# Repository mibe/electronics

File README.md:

# This repo contains some electronic projects of mine:

## Arduino
Some simple codes for the Arduino platform

## Blaulicht
Retrofitting an old toy car with emergency lights

## BreadBoard-Power-BusBar
Connect both opposing supply rails of a breadboard in an orderly fashion

## breakout_boards
Some breakout boards for use on a breadboard

## cookie-mouse
An automatic clicking mouse for the game Cookie Clicker

## Feuermelder
A USB "keyboard" disguised in the form of a fire call point to open the Windows Taskmanager

## Flip-USB
A replacement USB board for JBL's Flip 2 bluetooth speaker

## LCR-Shoe
A power supply attachment for cheap LCR meters

## StarPower
A control PCB for a christmas star as a replacement for the old, less energy-efficient one

## thunder-timer
A device to calculate thunderstorm distance by timing the interval between lightning and thunder

## tiny-UPDI-burner
A small board for connecting an USB to RS-232 converter to SOIC to DIL converters for burning ATtiny's via UPDI

## uCurrentCase
A case for Dave Jones' µCurrent GOLD

## USB-breaker
A tool to shortly disconnect a USB device from the USB bus

## Wire-to-RJ14
A simple adapter to connect bare wires to a cable with RJ-14 connectors

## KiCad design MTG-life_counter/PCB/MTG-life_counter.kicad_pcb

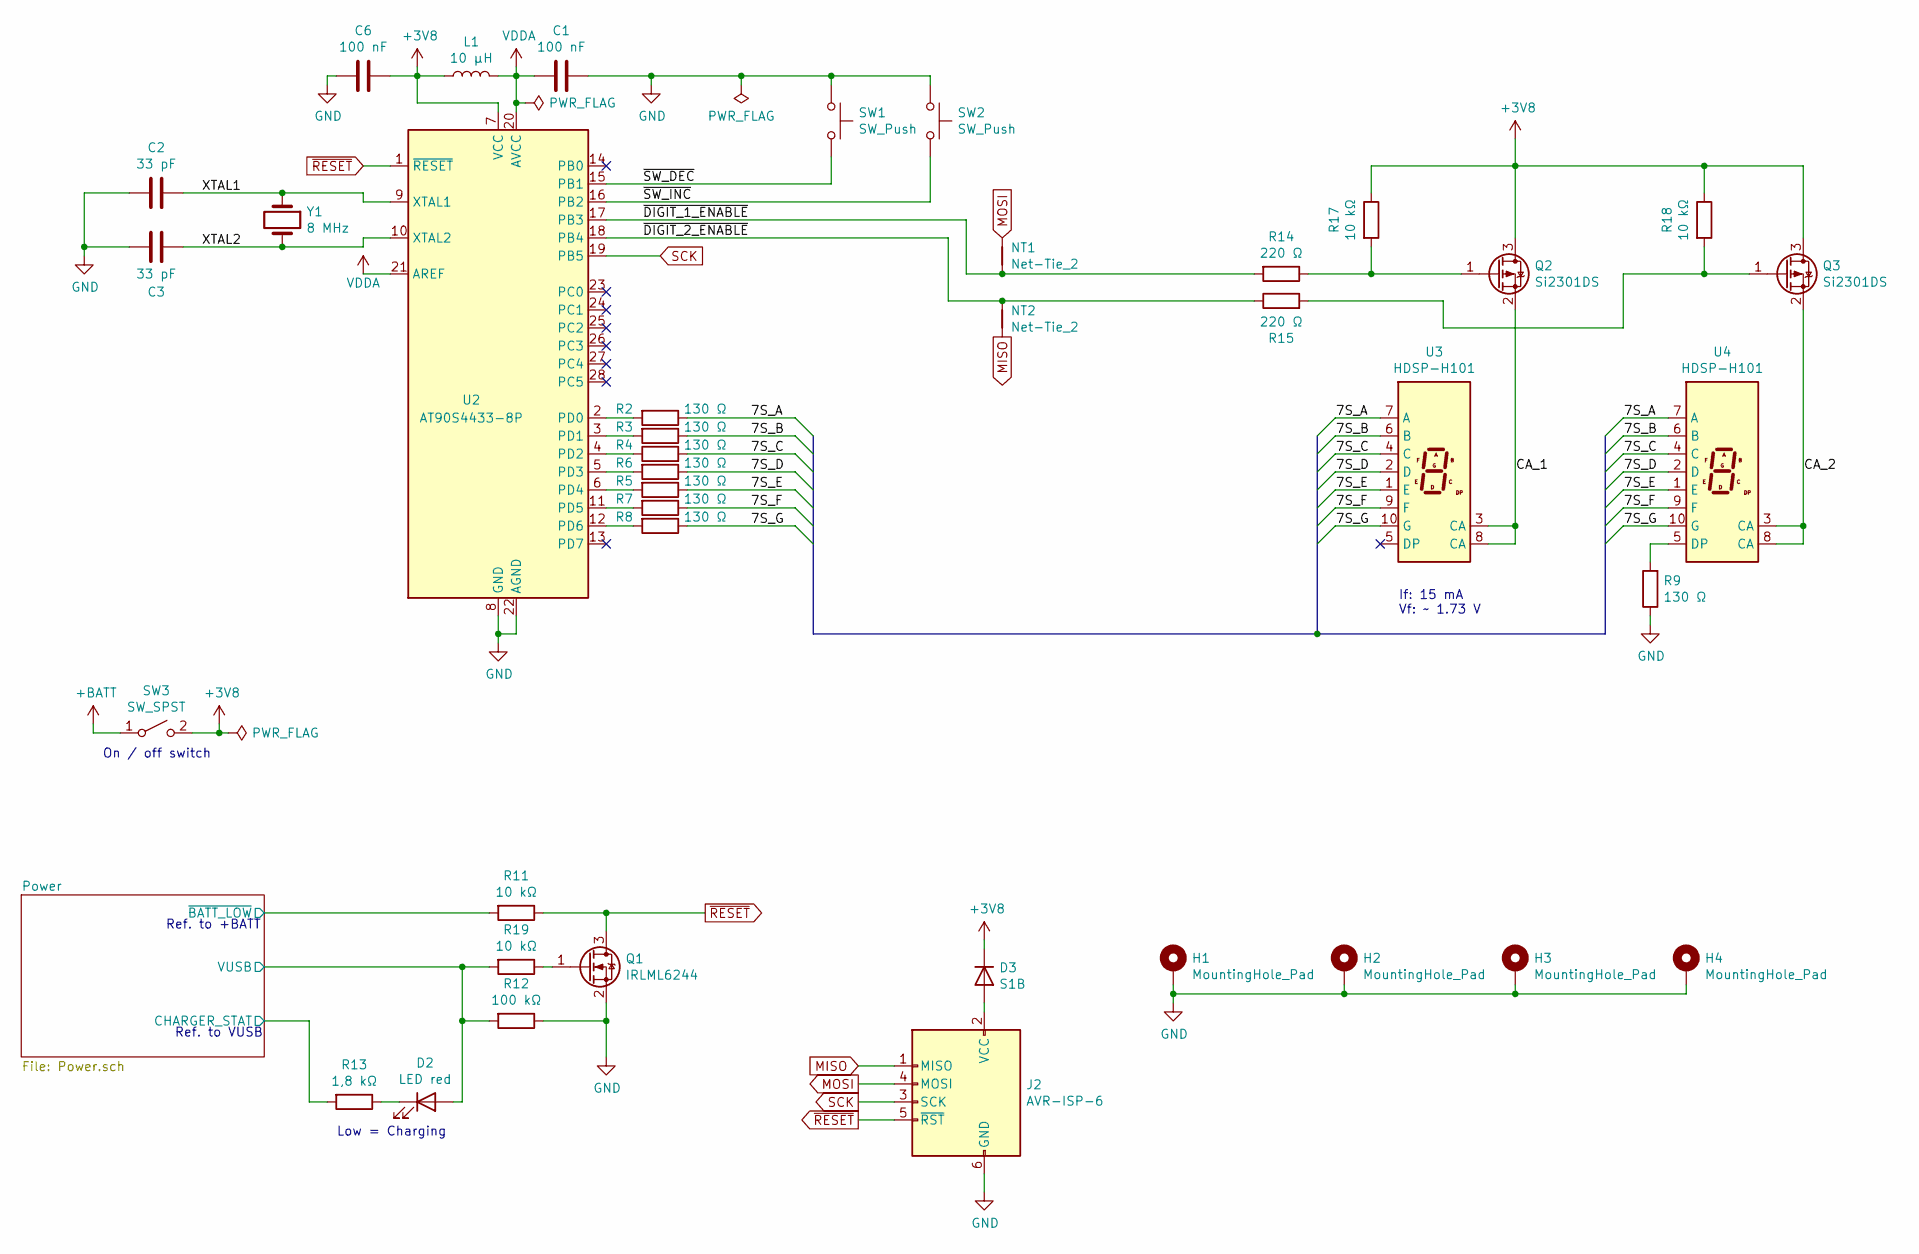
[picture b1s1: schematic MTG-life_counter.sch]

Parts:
C1, C6: 100 nF; C_0805_2012Metric_Pad1.18x1.45mm_HandSolder
C2, C3: 33 pF; C_1206_3216Metric_Pad1.42x1.75mm_HandSolder
D2: LED red; LED_D3.0mm_Horizontal_O1.27mm_Z2.0mm
D3: S1B; D_SMA_Handsoldering
H1, H2, H3, H4: MountingHole_Pad; SMTSO-M3
J2: AVR-ISP-6; PinHeader_2x03_P2.54mm_Vertical
L1: 10 µH; L_0805_2012Metric_Pad1.15x1.40mm_HandSolder
NT1, NT2: Net-Tie_2; NetTie-2_SMD_Pad0.25mm
Q1: IRLML6244; SOT-23_Handsoldering
Q2, Q3: Si2301DS; SOT-23_Handsoldering
R2, R3, R4, R5, R6, R7, R8, R9: 130 Ω; R_0805_2012Metric_Pad1.20x1.40mm_HandSolder
R11, R17, R18, R19: 10 kΩ; R_0805_2012Metric_Pad1.20x1.40mm_HandSolder
R12: 100 kΩ; R_0805_2012Metric_Pad1.20x1.40mm_HandSolder
R13: 1,8 kΩ; R_0805_2012Metric_Pad1.20x1.40mm_HandSolder
R14, R15: 220 Ω; R_0805_2012Metric_Pad1.20x1.40mm_HandSolder
SW1, SW2: SW_Push; SolderWire-0.15sqmm_1x02_P4mm_D0.5mm_OD1.5mm
SW3: SW_SPST; SolderWire-0.15sqmm_1x02_P4mm_D0.5mm_OD1.5mm
U2: AT90S4433-8P; DIP-28_W7.62mm
U3, U4: HDSP-H101
Y1: 8 MHz; Crystal_HC49-4H_Vertical

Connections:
+3V8: C6.1, D3.1 (K), L1.1, Q2.3 (D), Q3.3 (D), R17.1, R18.1, SW3.2 (B), U2.7 (VCC)
+BATT: SW3.1 (A); also elsewhere on the board
/7S_A: R2.1, U3.7 (A), U4.7 (A)
/7S_B: R3.1, U3.6 (B), U4.6 (B)
/7S_C: R4.2, U3.4 (C), U4.4 (C)
/7S_D: R5.1, U3.2 (D), U4.2 (D)
/7S_E: R6.1, U3.1 (E), U4.1 (E)
/7S_F: R7.1, U3.9 (F), U4.9 (F)
/7S_G: R8.1, U3.10 (G), U4.10 (G)
/CA_1: Q2.2 (S), U3.3 (CA), U3.8 (CA)
/CA_2: Q3.2 (S), U4.3 (CA), U4.8 (CA)
/Power/CHARGER_STAT: R13.2; also elsewhere on the board
/Power/VUSB: D2.2 (A), R12.2, R19.2; also elsewhere on the board
/Power/~BATT_LOW: R11.2; also elsewhere on the board
/XTAL1: C2.1, U2.9 (XTAL1), Y1.1
/XTAL2: C3.1, U2.10 (XTAL2), Y1.2
/~DIGIT_1_ENABLE: NT1.2, R14.2, U2.17 (PB3)
/~DIGIT_2_ENABLE: NT2.1, R15.1, U2.18 (PB4)
/~SW_DEC: SW1.2, U2.15 (PB1)
/~SW_INC: SW2.2, U2.16 (PB2)
GND: C1.1, C2.2, C3.2, C6.2, H1.1, H2.1, H3.1, H4.1, J2.6 (GND), Q1.2 (S), R9.1, R12.1, SW1.1, SW2.1, U2.8 (GND), U2.22 (AGND); also elsewhere on the board
MISO: J2.1 (MISO), NT2.2
MOSI: J2.4 (MOSI), NT1.1
unnamed: D2.1 (K), R13.1
unnamed: D3.2 (A), J2.2 (VCC)
unnamed: Q1.1 (G), R19.1
unnamed: Q2.1 (G), R14.1, R17.2
unnamed: Q3.1 (G), R15.2, R18.2
unnamed: R2.2, U2.2 (PD0)
unnamed: R3.2, U2.3 (PD1)
unnamed: R4.1, U2.4 (PD2)
unnamed: R5.2, U2.5 (PD3)
unnamed: R6.2, U2.6 (PD4)
unnamed: R7.2, U2.11 (PD5)
unnamed: R8.2, U2.12 (PD6)
unnamed: R9.2, U4.5 (DP)
SCK: J2.3 (SCK), U2.19 (PB5)
VDDA: C1.2, L1.2, U2.20 (AVCC), U2.21 (AREF)
~RESET: J2.5 (~RST), Q1.3 (D), R11.1, U2.1 (~RESET)

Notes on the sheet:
If: 15 mA Vf: ~~ 1.73 V
Ref. to +BATT
Ref. to VUSB
Low = Charging
On / off switch

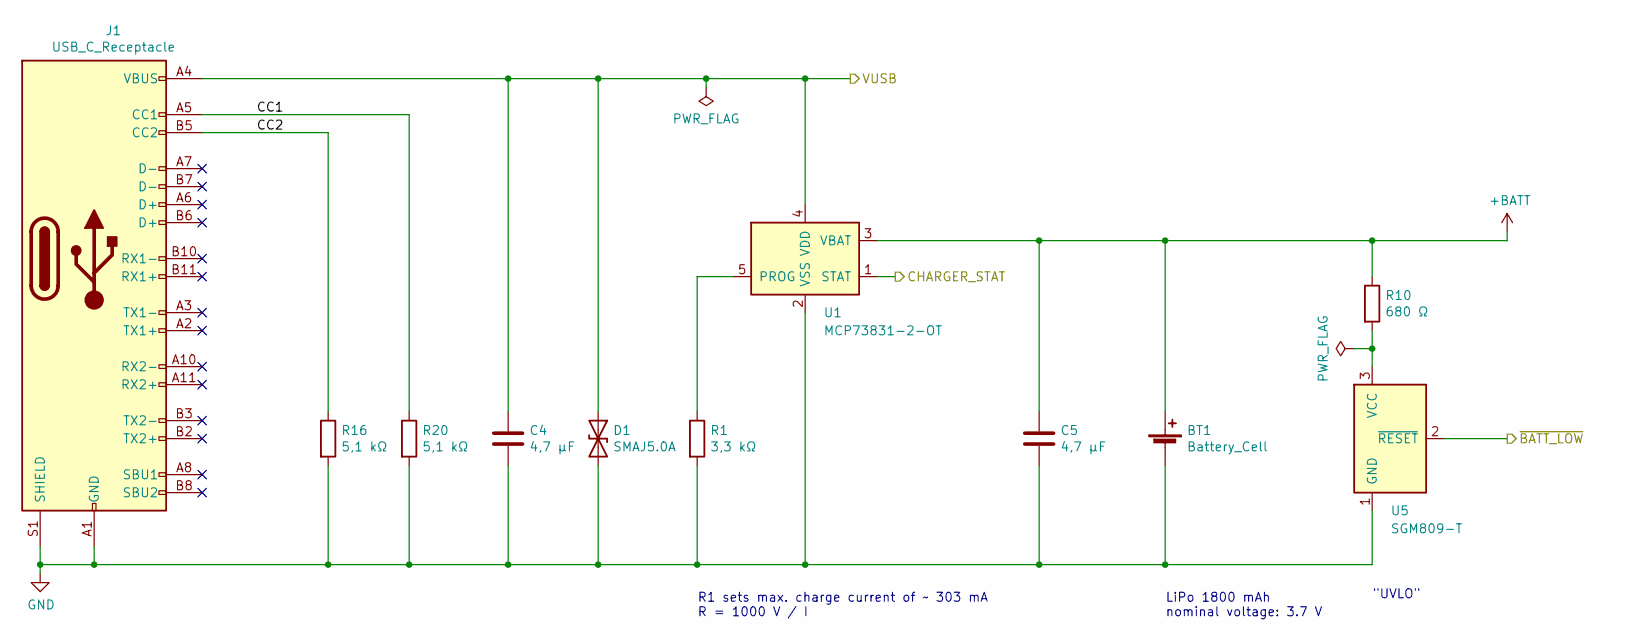
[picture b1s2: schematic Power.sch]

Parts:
BT1: Battery_Cell; PinHeader_1x02_P2.54mm_Horizontal
C4, C5: 4,7 µF; C_1206_3216Metric_Pad1.42x1.75mm_HandSolder
D1: SMAJ5.0A; D_SMA_Handsoldering
J1: USB_C_Receptacle; USB_C_Receptacle_Bellwether_80211-x92
R1: 3,3 kΩ; R_0805_2012Metric_Pad1.20x1.40mm_HandSolder
R10: 680 Ω; R_0805_2012Metric_Pad1.20x1.40mm_HandSolder
R16, R20: 5,1 kΩ; R_0805_2012Metric_Pad1.20x1.40mm_HandSolder
U1: MCP73831-2-OT; SOT-23-5
U5: SGM809-T; SOT-23W_Handsoldering

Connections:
+BATT: BT1.1 (+), C5.1, R10.1, U1.3 (VBAT); also elsewhere on the board
/Power/CC1: J1.A5 (CC1), R20.1
/Power/CC2: J1.B5 (CC2), R16.1
/Power/CHARGER_STAT: U1.1 (STAT); also elsewhere on the board
/Power/VUSB: C4.1, D1.1 (A1), J1.A4 (VBUS), J1.A9 (VBUS), J1.B4 (VBUS), J1.B9 (VBUS), U1.4 (VDD); also elsewhere on the board
/Power/~BATT_LOW: U5.2 (~RESET); also elsewhere on the board
GND: BT1.2 (-), C4.2, C5.2, D1.2 (A2), J1.A1 (GND), J1.A12 (GND), J1.B1 (GND), J1.B12 (GND), J1.S1 (SHIELD), R1.2, R16.2, R20.2, U1.2 (VSS), U5.1 (GND); also elsewhere on the board
unnamed: R1.1, U1.5 (PROG)
unnamed: R10.2, U5.3 (VCC)

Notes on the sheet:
LiPo 1800 mAh nominal voltage: 3.7 V
R1 sets max. charge current of ~~ 303 mA R = 1000 V / I
"UVLO"

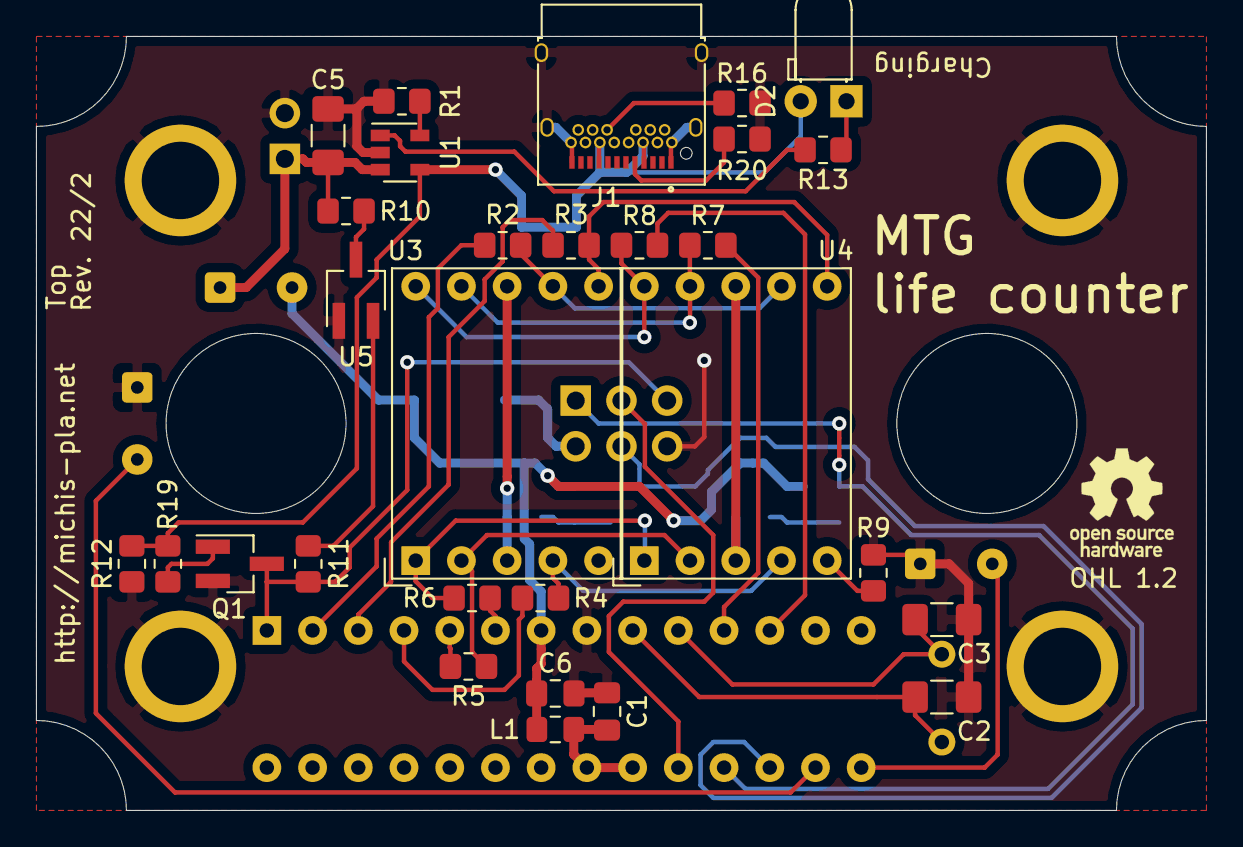
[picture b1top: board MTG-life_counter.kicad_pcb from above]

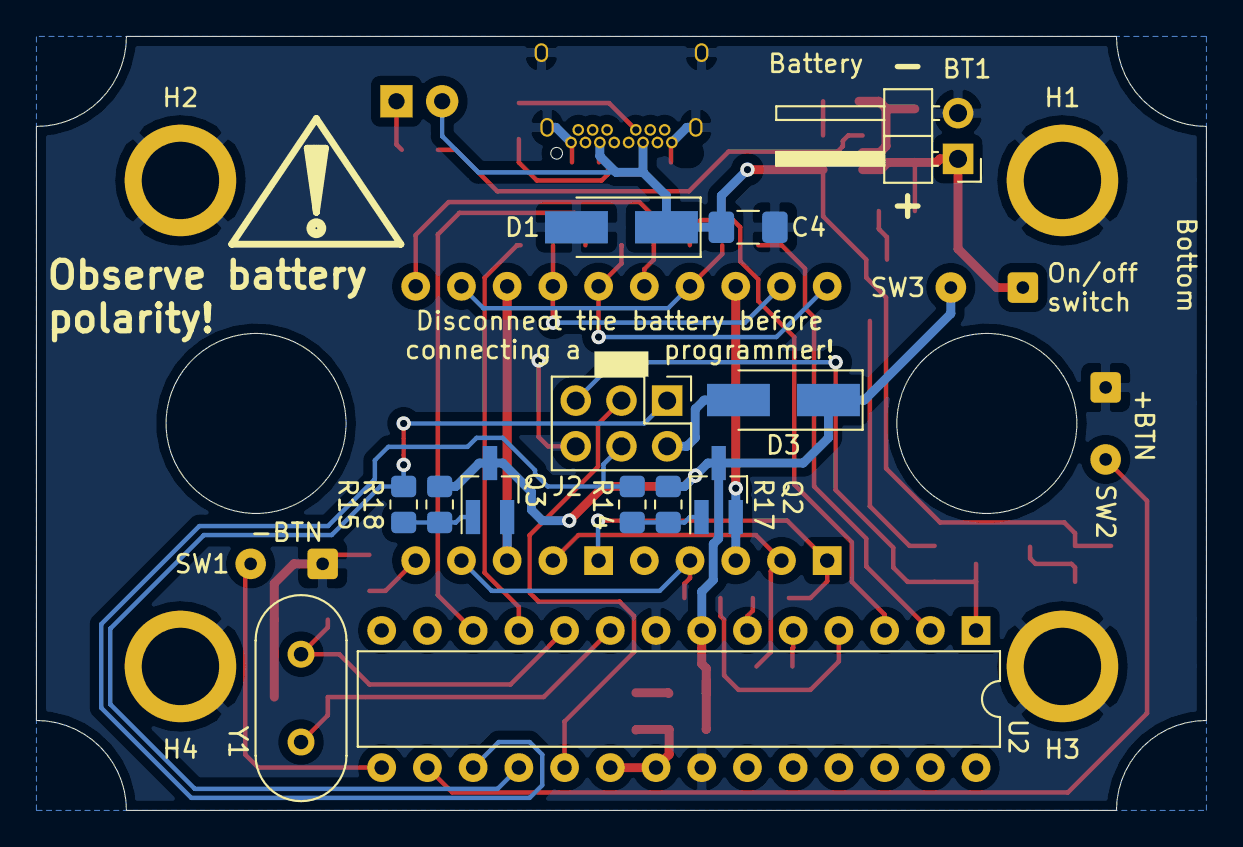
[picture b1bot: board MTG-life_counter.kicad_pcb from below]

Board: 2 copper layers, 65.0 x 43.0 mm, 51 parts (18 on the bottom side), 43 nets.

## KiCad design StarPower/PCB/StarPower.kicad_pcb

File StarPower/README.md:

# StarPower
"StarPower" is a PCB to drive one of these cheap Moravian star christmas decorations. The original circuit drives 12 LEDs in parallel and uses a dropper resistor. That means about ⅓ of the supply voltage is wasted as heat, which is way too much for a battery powered system. The new circuit uses an LED driver (PAM2804 from Diodes Inc.), which is a step-down DC/DC converter with only 0.1 V feedback voltage. As an added bonus this new circuit supports NiMH rechargeable batteries: A battery monitor resets the system at about 3 V, so the three cells cut-off at about 1 V each. The microcontroller is clocked by a 32.768 kHz crystal and has as many features as possible disabled and runs in sleep mode to save power. The µC consumes about 12 µA.

## Parameters
* Voltage range: 3 V - 4.5 V
* LED current: 120 mA
* LED forward voltage: 2.8 V
* LEDs driven in parallel: 12

## Bill of Materials
See the ```PCB\bom.html``` file.

## License
(C) 2022 Michael Bemmerl

This PCB is available under the [CERN OHL 1.2 License](https://www.ohwr.org/project/cernohl/wikis/Documents/CERN-OHL-version-1.2) license.

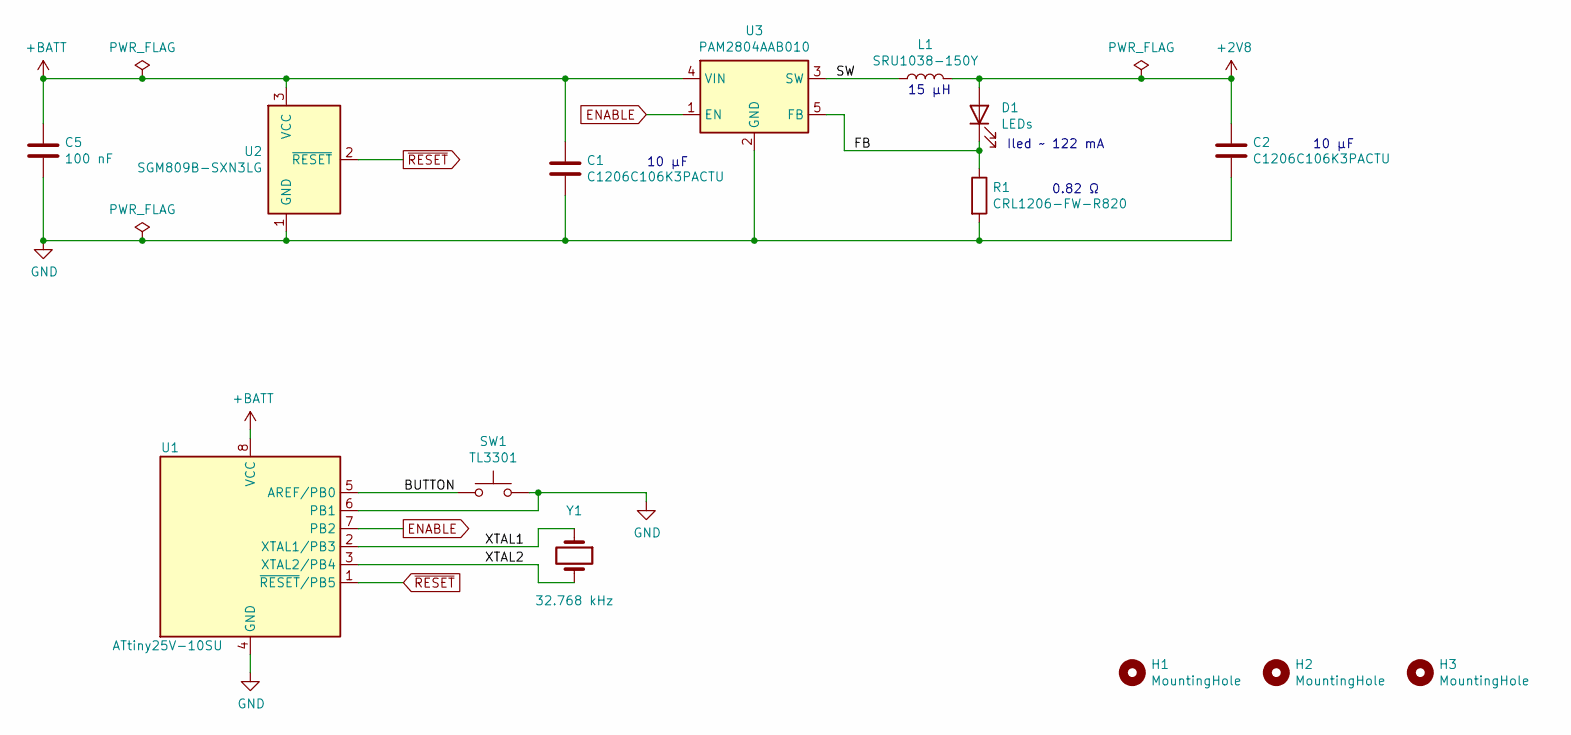
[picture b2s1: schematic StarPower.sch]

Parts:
C1, C2: C1206C106K3PACTU; C_1206_3216Metric_Pad1.42x1.75mm_HandSolder
C5: 100 nF; C_0805_2012Metric_Pad1.18x1.45mm_HandSolder
D1: LEDs
H1, H2: MountingHole; MountingHole_3.5mm
H3: MountingHole; MountingHole_2.5mm
L1: SRU1038-150Y; L_Bourns-SRU1028_10.0x10.0mm
R1: CRL1206-FW-R820; R_1206_3216Metric_Pad1.30x1.75mm_HandSolder
SW1: TL3301; SW_SPST_TL3301
U1: ATtiny25V-10SU; SOIJ-8_5.3x5.3mm_P1.27mm
U2: SGM809B-SXN3LG; SOT-23W_Handsoldering
U3: PAM2804AAB010; TSOT-23-5
Y1: 32.768 kHz; Crystal_SMD_Qantek_QTP7-4Pin_6.9x1.4mm_HandSoldering

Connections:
+2V8: C2.1, D1.2 (A), L1.2
+BATT: C1.1, C5.1, U1.8 (VCC), U2.3 (VCC), U3.4 (VIN)
/BUTTON: SW1.1, U1.5 (AREF/PB0)
/FB: D1.1 (K), R1.1, U3.5 (FB)
/SW: L1.1, U3.3 (SW)
/XTAL1: U1.2 (XTAL1/PB3), Y1.1
/XTAL2: U1.3 (XTAL2/PB4), Y1.2
ENABLE: U1.7 (PB2), U3.1 (EN)
GND: C1.2, C2.2, C5.2, R1.2, SW1.2, U1.4 (GND), U1.6 (PB1), U2.1 (GND), U3.2 (GND)
~RESET: U1.1 (~RESET~/PB5), U2.2 (~RESET)

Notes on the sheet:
15 µH
10 µF
0.82 Ω
Iled ~~ 122 mA

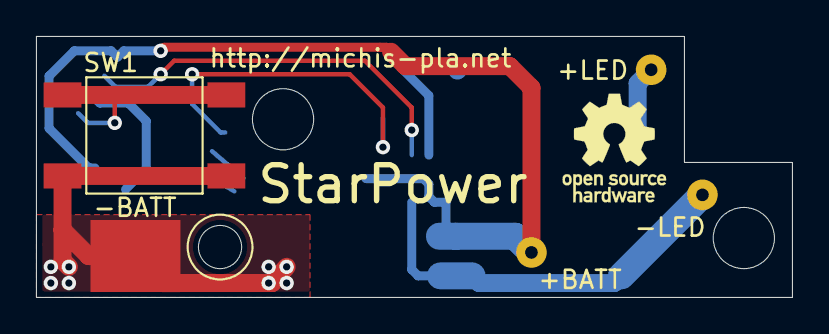
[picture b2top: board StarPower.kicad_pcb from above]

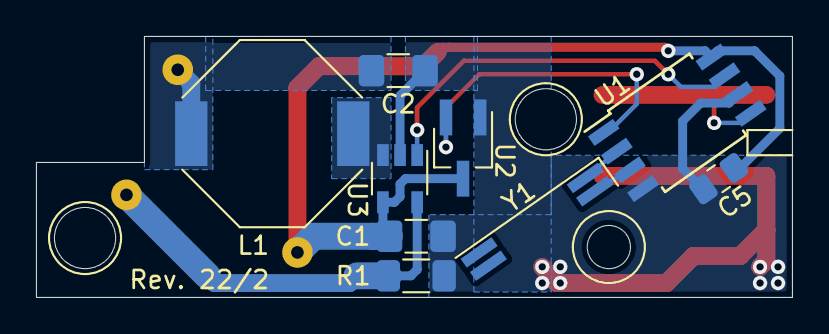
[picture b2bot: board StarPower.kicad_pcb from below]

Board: 2 copper layers, 42.0 x 14.5 mm, 13 parts (9 on the bottom side), 10 nets.

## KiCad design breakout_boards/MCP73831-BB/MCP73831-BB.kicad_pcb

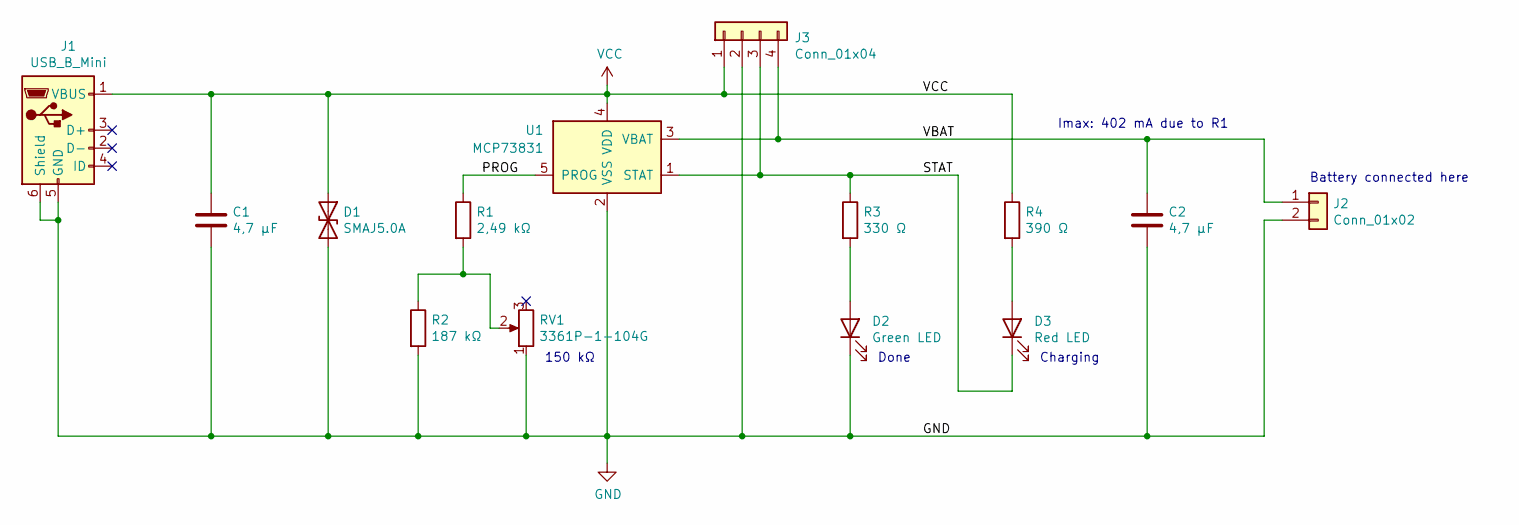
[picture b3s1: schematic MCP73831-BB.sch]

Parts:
C1, C2: 4,7 µF; C_1206_3216Metric_Pad1.42x1.75mm_HandSolder
D1: SMAJ5.0A; D_SMA_Handsoldering
D2: Green LED; LED_1206_3216Metric_Pad1.42x1.75mm_HandSolder
D3: Red LED; LED_1206_3216Metric_Pad1.42x1.75mm_HandSolder
J1: USB_B_Mini; USB_Mini-B_Reichelt_BWM
J2: Conn_01x02; JST_PH_B2B-PH-K_1x02_P2.00mm_Vertical
J3: Conn_01x04; PinHeader_1x04_P2.54mm_Vertical
R1: 2,49 kΩ; R_0805_2012Metric_Pad1.20x1.40mm_HandSolder
R2: 187 kΩ; R_0805_2012Metric_Pad1.20x1.40mm_HandSolder
R3: 330 Ω; R_0805_2012Metric_Pad1.20x1.40mm_HandSolder
R4: 390 Ω; R_0805_2012Metric_Pad1.20x1.40mm_HandSolder
RV1: 3361P-1-104G; Potentiometer_Bourns_3361P_Vertical
U1: MCP73831; SOT-23-5

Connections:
/PROG: R1.1, U1.5 (PROG)
/STAT: D3.1 (K), J3.3, R3.1, U1.1 (STAT)
/VBAT: C2.1, J2.1, J3.4, U1.3 (VBAT)
GND: C1.2, C2.2, D1.2 (A2), D2.1 (K), J1.5 (GND), J1.6 (Shield), J2.2, J3.2, R2.2, RV1.1, U1.2 (VSS)
unnamed: D2.2 (A), R3.2
unnamed: D3.2 (A), R4.2
unnamed: R1.2, R2.1, RV1.2
VCC: C1.1, D1.1 (A1), J1.1 (VBUS), J3.1, R4.1, U1.4 (VDD)

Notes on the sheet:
Imax: 402 mA due to R1
Battery connected here
150 kΩ
Charging
Done

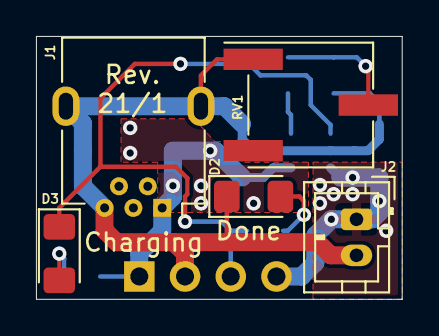
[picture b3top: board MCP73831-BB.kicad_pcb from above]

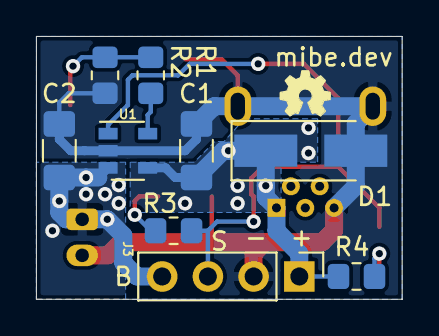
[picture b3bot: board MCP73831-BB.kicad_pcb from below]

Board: 2 copper layers, 20.3 x 14.6 mm, 14 parts (9 on the bottom side), 8 nets.

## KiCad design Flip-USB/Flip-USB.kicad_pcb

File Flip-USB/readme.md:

A replacement USB connector board for JBL's Flip 2 bluetooth speaker, using a Hirose ZX62D-B-5PA8(30) Micro B connector.

The board must have a thickness of 1 mm, otherwise it won't fit into the case of the speaker.

On the original board were two footprints, probably resistors, which were not placed.

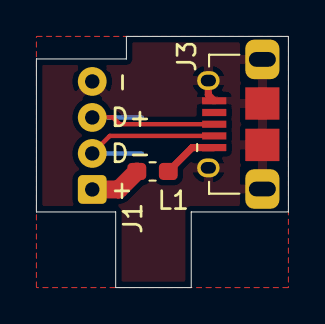
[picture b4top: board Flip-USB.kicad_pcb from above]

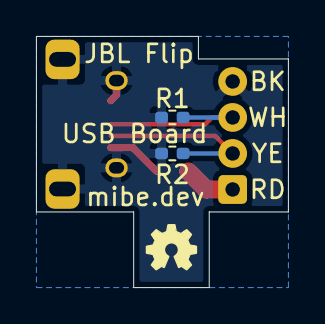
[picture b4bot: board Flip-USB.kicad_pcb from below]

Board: 2 copper layers, 14.0 x 14.0 mm, 5 parts (2 on the bottom side), 5 nets.

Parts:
J1: Conn_01x04; SolderWire-0.15sqmm_1x04_P2mm_D0.5mm_OD1.5mm
J3: ZX62D-B-5PA8(30); USB_Micro_B_Hirose_ZX62D-B-5PA8
L1: ?; L_0603_1608Metric_Pad1.05x0.95mm_HandSolder
R1, R2: R; R_0402_1005Metric_Pad0.72x0.64mm_HandSolder

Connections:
/D+: J1.3, J3.3, R1.1
/D-: J1.2, J3.2, R2.1
/VCC_USB: J3.1, L1.2
GND: J1.4, J3.5, J3.6, R1.2, R2.2
VCC: J1.1, L1.1

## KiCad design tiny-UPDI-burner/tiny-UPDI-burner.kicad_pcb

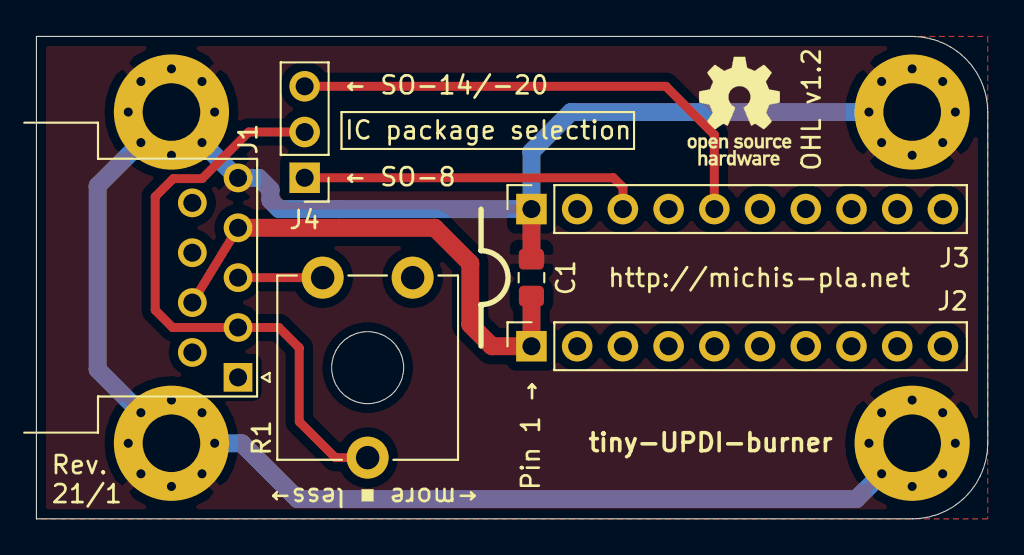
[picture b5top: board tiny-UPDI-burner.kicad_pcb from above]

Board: 2 copper layers, 52.9 x 26.8 mm, 10 parts (0 on the bottom side), 6 nets.

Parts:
C1: 100n; C_0805_2012Metric_Pad1.15x1.40mm_HandSolder
H1, H2, H3, H4: MountingHole_Pad; MountingHole_3.2mm_M3_Pad_Via
J1: DB9_Female; DSUB-9_Female_Horizontal_P2.77x2.54mm_EdgePinOffset9.40mm
J2, J3: Conn_01x10_Female; PinSocket_1x10_P2.54mm_Vertical
J4: Conn_01x03_Male; PinHeader_1x03_P2.54mm_Vertical
R1: 10k; Potentiometer_ACP_CA9-V10_Vertical_Hole

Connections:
/RxD: J1.2, J4.2, R1.2
/TxD: J1.3, R1.1
/UPDI_8: J3.3, J4.1
/UPDI_14-20: J3.5, J4.3
GND: C1.2, H1.1, H2.1, H3.1, H4.1, J1.5, J3.1
VCC: C1.1, J1.4, J1.7, J2.1

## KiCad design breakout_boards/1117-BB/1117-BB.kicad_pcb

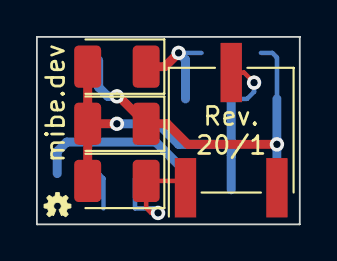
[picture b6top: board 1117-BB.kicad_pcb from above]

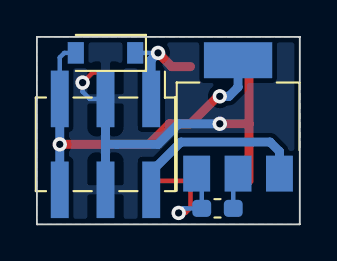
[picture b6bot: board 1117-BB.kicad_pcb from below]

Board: 2 copper layers, 14.6 x 10.4 mm, 8 parts (4 on the bottom side), 4 nets.

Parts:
C1: TAJB106K020SNJ; CP_EIA-3528-21_Kemet-B_Pad1.50x2.35mm_HandSolder
C2, C3: TAJB226K020RNJV; CP_EIA-3528-21_Kemet-B_Pad1.50x2.35mm_HandSolder
D1: SD103BW; D_SOD-123
J1: Conn_02x03_Odd_Even; PinHeader_2x03_P2.54mm_Vertical_SMD
R1: 150; R_0603_1608Metric_Pad1.05x0.95mm_HandSolder
R2: 3361P-1-202GLF; Potentiometer_Bourns_3361P_Vertical
U1: LT1117-ADJ; SOT-223-3_TabPin2

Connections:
/ADJ: C3.1, R1.2, R2.1, U1.1
GND: C1.2, C2.2, C3.2, J1.3, J1.4, R2.2
VBUS: C1.1, D1.1, J1.1, J1.2, U1.3
VCC: C2.1, D1.2, J1.5, J1.6, R1.1, U1.2

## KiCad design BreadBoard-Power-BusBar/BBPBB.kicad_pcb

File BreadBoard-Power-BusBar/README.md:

# BreadBoard-Power-BusBar
The BBPBB is a PCB to connect both supply rails on a standard breadboard. As a bonus the PCB has an LED to indicate power on the rails. This LED can be switched off if it becomes too distracting. The PCB is non-polarized, so the direction how the BBPBB is plugged into the breadboard does not matter.

## Range
Voltage range: 3 V - 30 V
Maximum current: 5 A

## Bill of Materials
See the ```BBPBB.csv``` or ```bom.html``` file.

## License
(C) 2020 Michael Bemmerl

This PCB is available under the [CERN OHL 1.2 License](https://www.ohwr.org/project/cernohl/wikis/Documents/CERN-OHL-version-1.2) license.

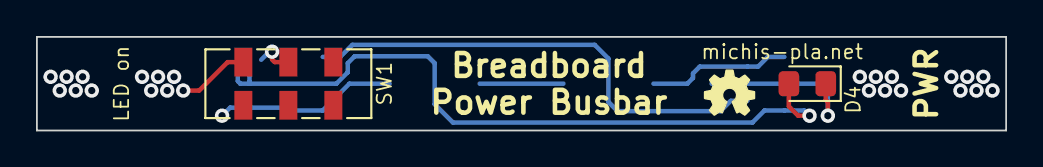
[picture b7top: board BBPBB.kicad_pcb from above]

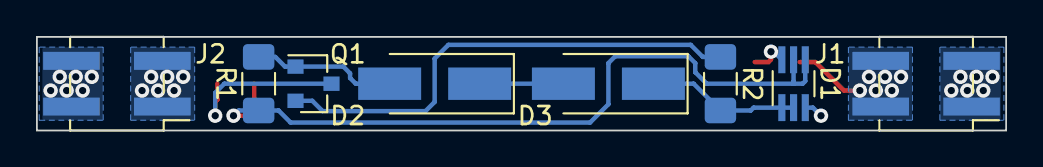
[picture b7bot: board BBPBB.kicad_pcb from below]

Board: 4 copper layers, 53.8 x 5.2 mm, 10 parts (8 on the bottom side), 9 nets.

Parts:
D1: BAS40BRW; SOT-363_SC-70-6_Handsoldering
D2, D3: S1B; D_SMA_Handsoldering
D4: 17-21SYGC; LED_0805_2012Metric_Pad1.15x1.40mm_HandSolder
J1, J2: Conn_02x02_Odd_Even; PinHeader_2x02_P2.54mm_Vertical_SMD
Q1: BC847B; SOT-23
R1: 1k; R_1206_3216Metric_Pad1.42x1.75mm_HandSolder
R2: 150; R_1206_3216Metric_Pad1.42x1.75mm_HandSolder
SW1: JS102011JCQN; SW_DPDT_CK_JS202011JCQN

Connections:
/Power-1: J1.2, J1.4, J2.2, J2.4, SW1.3
/Power-2: D1.3, J1.1, J1.3, J2.1, J2.3
GND: D1.1, D1.2, D3.1, R2.2
unnamed: D1.6, SW1.2
unnamed: D2.1, D3.2
unnamed: D2.2, Q1.1, R1.2
unnamed: D4.1, Q1.3
unnamed: Q1.2, R2.1
VCC: D1.4, D1.5, D4.2, R1.1

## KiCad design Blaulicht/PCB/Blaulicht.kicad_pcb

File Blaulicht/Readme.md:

# Blaulicht
The idea was to retrofit an old toy car with some blinkenlights imitating emergency lighting from the real world. The blink pattern was taken off of a YouTube video I cannot find anymore.

# License
(C) 2020 Michael Bemmerl

This PCB is available under the [CERN OHL 1.2 License](https://www.ohwr.org/project/cernohl/wikis/Documents/CERN-OHL-version-1.2) license, while the firmware is [MIT](https://opensource.org/licenses/MIT) licensed.

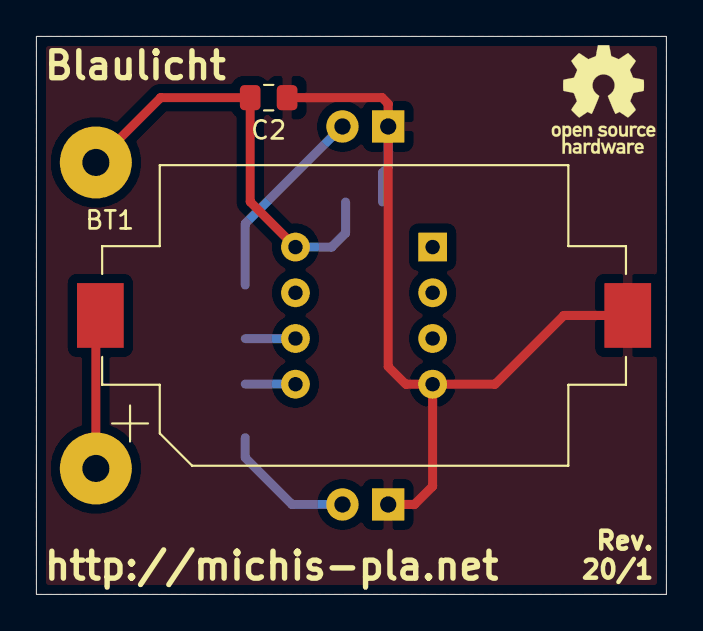
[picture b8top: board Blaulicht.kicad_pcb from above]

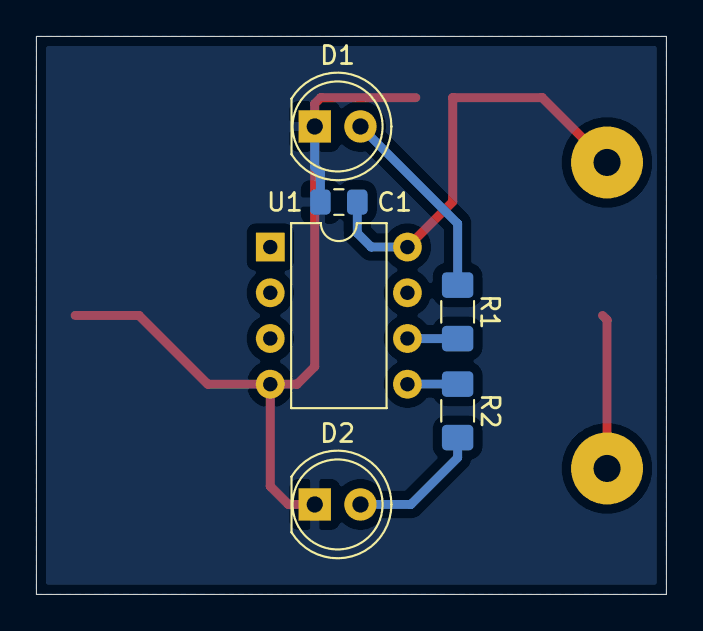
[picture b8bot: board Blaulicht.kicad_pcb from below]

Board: 2 copper layers, 35.0 x 31.0 mm, 8 parts (6 on the bottom side), 6 nets.

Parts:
BT1: CR2032 3V; BatteryHolder_Keystone_1060_1x2032
C1: 100n; C_0805_2012Metric_Pad1.15x1.40mm_HandSolder
C2: 2.2µ; C_0805_2012Metric_Pad1.15x1.40mm_HandSolder
D1, D2: LED; LED_D5.0mm
R1, R2: 20; R_1206_3216Metric_Pad1.42x1.75mm_HandSolder
U1: ATtiny45V-10PU; DIP-8_W7.62mm

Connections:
/I_D1: D1.2, R1.2
/I_D2: D2.2, R2.2
/PB1: R1.1, U1.6
/PB2: R2.1, U1.5
GND: BT1.2, C1.2, C2.2, D1.1, D2.1, U1.4
VCC: C1.1, C2.1, U1.8

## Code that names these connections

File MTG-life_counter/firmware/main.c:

#include <avr/io.h>
#include <util/delay.h>
#include <avr/interrupt.h>
#include <avr/pgmspace.h>

/**
 * Counter values:
 */
#define MAX			99			// Maximum counter value
#define MIN			0			// Minimum counter value
#define START		20			// Starting counter value
#define START_THG	30			// Starting counter value for Two-Headed Giant
#define INJURED		10			// "Breathing" animation counter value

/**
 * Pin mappings:
 */
#define INC_BTN		PB1			// Button for incrementing the counter value
#define DEC_BTN		PB2			// Button for decrementing the counter value
#define DIGIT1		PB3			// Anode driver for first digit
#define DIGIT2		PB4			// Anode driver for second digit

/**
 * State variable of the Dead ticker-style animation
 *
 * Content: 0xCCCX XXBA  (LSB 0)
 *   CCC = animation index
 *     B = zero counter was displayed
 *     A = overall dead state
 */
uint8_t isDead = 0;

/**
 * State variable for the breathing animation. Set when the counter is not greather than INJURED.
 */
uint8_t isInjured = 0;

/**
 * Life counter, set to START
 */
uint8_t counter = START;

/**
 * Variables containing the bits for the 7-segment display for the digits.
 */
uint8_t digit1 = 0;
uint8_t digit2 = 0;

/**
 * State variables for the ticker and the breathing animation.
 */
volatile uint8_t origPORTD = 0;
volatile uint8_t breathDirection = 0;
volatile uint8_t breathStep = 0;
volatile uint8_t breathIndex = 0;
volatile uint8_t timer1Compare = 0;
volatile uint8_t timer1Counter = 0;
volatile uint8_t tickerCounter = 0;

const uint8_t digits[10] PROGMEM = {63, 6, 91, 79, 102, 109, 125, 7, 127, 111}; // "0123456789"
const uint8_t dead[7] PROGMEM = {0, 94, 121, 119, 94, 0, 0}; // " dEAd  "
const uint8_t breath[21] PROGMEM = {0, 0, 0, 1, 1, 2, 3, 4, 6, 8, 10, 12, 15, 18, 21, 22, 23, 24, 25, 25, 25}; // breath curve: inhale; backwards exhale
const uint8_t btnMask = _BV(INC_BTN) | _BV(DEC_BTN);

ISR(TIMER0_OVF_vect)
{
	// Multiplex both 7-segment displays:
	// Switch active digit, depending on which one is active.
	if ((PORTB & _BV(DIGIT1)) == _BV(DIGIT1))
	{
		// disable second, enable first
		PORTB &= ~_BV(DIGIT1);
		PORTB |= _BV(DIGIT2);
		
		PORTD = digit1;
	}
	else
	{
		// disable first, enable second
		PORTB |= _BV(DIGIT1);
		PORTB &= ~_BV(DIGIT2);
		
		PORTD = digit2;
	}
	
	// Backup PORTD. This is used in the TIMER1_COMP ISR.
	origPORTD = PORTD;
	
	if (isDead)
		tickerCounter++;
	
	if (isInjured)
	{
		// Next "breath" index every 10th step
		if (breathStep == 10)
		{
			timer1Compare = pgm_read_byte(&(breath[breathIndex]));
			
			// Increment or decrement the index depending on the direction and swap it when needed.
			if (breathDirection == 0)
			{
				if (breathIndex == 20)
					breathDirection = 1;
				else
					breathIndex++;
			}
			else
			{
				if (breathIndex == 0)
					breathDirection = 0;
				else
					breathIndex--;
			}
			
			// Reset step
			breathStep = 0;
		}
		else
			breathStep++;
	}
}

ISR(TIMER1_COMP_vect)
{
	// Enable all segments when the counter is smaller than timer1Compare.
	// Otherwise use original PORTD value. This is basically a software PWM.
	if (timer1Counter < timer1Compare)
		PORTD = 0x0;
	else
		PORTD = origPORTD;
	
	timer1Counter++;
}

void calc_digits()
{
	uint8_t temp = counter;
	uint8_t tenths = 0;
	
	while(temp >= 10)
	{
		tenths++;
		temp -= 10;
	}
	
	if (tenths > 0)
		digit1 = ~pgm_read_byte(&(digits[tenths]));
	else
		digit1 = 0xFF;
	
	digit2 = ~pgm_read_byte(&(digits[temp]));
}

void update_display()
{
	// Is the player dead?
	if (isDead)
	{
		// Player is dead, do the ticker
		// Wait one animation cycle to display the zero. Bit two used here as state.
		if ((isDead & 0x02) == 0x00)
		{
			calc_digits();
			isDead = 0x03;
		}
		else
		{
			// Get index from the three MSB bits (mask & shift)
			uint8_t index = (isDead & 0xE0) >> 5;
			digit1 = ~pgm_read_byte(&(dead[index++]));
			digit2 = ~pgm_read_byte(&(dead[index]));
			
			// Reset index if necessary
			if (index >= 6)
				index = 0;
			
			// Save index in state variable
			isDead = (index << 5) | 0x03;
		}
	}
	else
		calc_digits();
}

void start_breathing()
{
	isInjured = 1;
	
	// Timer1 runs at clock speed.
	TCCR1B |= _BV(CS10);
}

void stop_breathing()
{
	// Reset state variables
	isInjured = 0;
	breathDirection = 0;
	breathStep = 0;
	breathIndex = 0;
	timer1Compare = 0;
	timer1Counter = 0;
	
	// Stop Timer1
	TCCR1B &= ~_BV(CS10);
}

void setup(void)
{
	// Set both anode drivers of the digits as outputs. Port D is also an output.
	DDRB |= _BV(DIGIT1) | _BV(DIGIT2);
	DDRD = 0xFF;
	
	// Enable pull-ups on both pins for the push buttons and the unused pins on Port B.
	// Also enable pull-ups on Port C and set all Port D pins high (disable display).
	PORTB |= _BV(INC_BTN) | _BV(DEC_BTN) | _BV(PB0) | _BV(PB5);
	PORTC = 0xFF;
	PORTD = 0xFF;
	
	calc_digits();
	
	// Disable Analog Comparator
	ACSR |= _BV(ACD);
	
	// Timer0 is used for multiplexing both 7-segment displays at ~ 488 Hz.
	// Prescaler of 64 (125 kHz)
	TCCR0 = _BV(CS02);
	
	// Timer1 is used for a "breathing" animation (but not started here).
	// Set output compare to 0xFF and to clear Timer1 at a match.
	OCR1 = 0xFF;
	TCCR1B = _BV(CTC1);
	
	// Enable interrupt handlers: Timer0 overflow & Timer1 compare match
	TIMSK |= _BV(TOIE0) | _BV(OCIE1);
	
	sei();
}

uint8_t debounce(uint8_t bit, uint8_t cancelBit)
{
	uint8_t canceled = 0;
	
	// Poor man's debouncing: Just wait until the button is not pressed anymore
	_delay_ms(100);
	while((PINB & _BV(bit)) == 0)
	{
		// Abort the loop when the cancel pin is low (button is pressed). Also check for a valid pin bit value.
		if (cancelBit <= 0x80 && (PINB & _BV(cancelBit)) == 0)
		{
			canceled = 1;
			break;
		}
	}
	
	if (!canceled)
		_delay_ms(50);
	
	return canceled;
}

int main(void)
{
	setup();
	
	while(1)
	{
		// Get button state
		uint8_t input = PINB & btnMask;
		
		if (input != btnMask)
		{
			if ((input & _BV(INC_BTN)) == 0)
			{
				if (counter < MAX)
					counter++;
				
				uint8_t both = debounce(INC_BTN, DEC_BTN);
				
				// If both buttons were pressed, reset the counter.
				if (both)
				{
					counter = START;
					debounce(INC_BTN, 0xFF);
					debounce(DEC_BTN, 0xFF);
				}
			}
			else if ((input & _BV(DEC_BTN)) == 0)
			{
				if (counter > MIN)
					counter--;
				
				uint8_t both = debounce(DEC_BTN, INC_BTN);
				
				// If both buttons were pressed, reset the counter to the Two-Headed Giant starting value.
				if (both)
				{
					counter = START_THG;
					debounce(INC_BTN, 0xFF);
					debounce(DEC_BTN, 0xFF);
				}
			}
			
			// If the counter reaches MIN, start the ticker animation.
			// If the counter is (once again) greater than MIN, disable the animation.
			if (counter == MIN)
			{
				isDead = 1;
				stop_breathing();
			}
			else
			{
				tickerCounter = 0;
				isDead = 0;
			}
			
			// If the counter is greater than MIN but less or equal INJURED start the breathing animation.
			// If not, stop it.
			if (counter > MIN && counter <= INJURED)
				start_breathing();
			else
				stop_breathing();
			
			update_display();
		}
		
		// The counter at 0x7F results in a nice ticker animation (~ 1 Hz)
		if (tickerCounter == 0x7F)
		{
			update_display();
			tickerCounter = 0;
		}
	}
	
	return 0;
}

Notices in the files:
Blaulicht/PCB/Blaulicht.kicad_pcb:
Open Hardware: CERN OHL v1.2
